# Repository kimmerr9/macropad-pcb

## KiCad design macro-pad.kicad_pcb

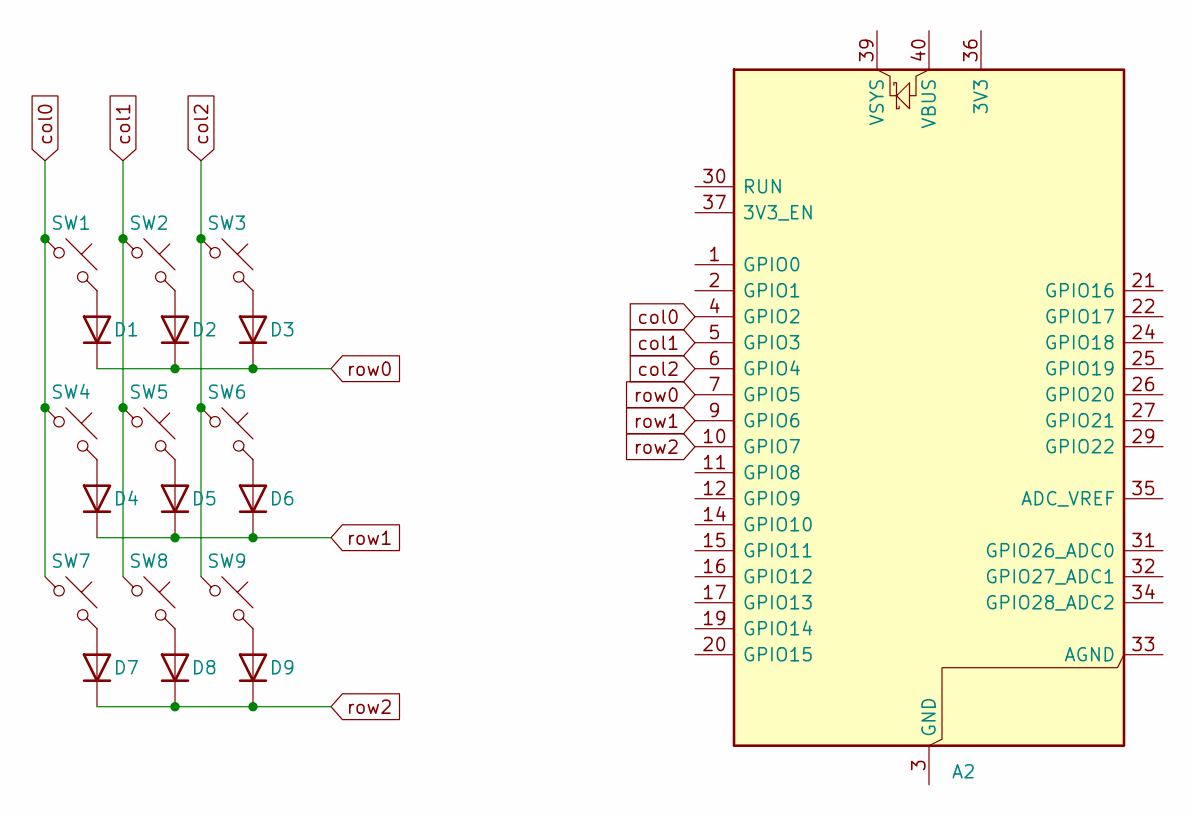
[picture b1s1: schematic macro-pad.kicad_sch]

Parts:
A2: RaspberryPi_Pico_W; RaspberryPi_Pico_W_SMD_HandSolder
D1, D2, D3, D4, D5, D6, D7, D8, D9: 1N4148; D_DO-35_SOD27_P7.62mm_Horizontal
SW1, SW2, SW3, SW4, SW5, SW6, SW7, SW8, SW9: SW_Push_45deg; SW_Cherry_MX_1.00u_PCB

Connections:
unnamed: A2.3 (GND), A2.8 (GND), A2.13 (GND), A2.18 (GND), A2.23 (GND), A2.28 (GND), A2.38 (GND)
unnamed: D1.2 (A), SW1.2
unnamed: D2.2 (A), SW2.2
unnamed: D3.2 (A), SW3.2
unnamed: D4.2 (A), SW4.2
unnamed: D5.2 (A), SW5.2
unnamed: D6.2 (A), SW6.2
unnamed: D7.2 (A), SW7.2
unnamed: D8.2 (A), SW8.2
unnamed: D9.2 (A), SW9.2
col0: A2.4 (GPIO2), SW1.1, SW4.1, SW7.1
col1: A2.5 (GPIO3), SW2.1, SW5.1, SW8.1
col2: A2.6 (GPIO4), SW3.1, SW6.1, SW9.1
row0: A2.7 (GPIO5), D1.1 (K), D2.1 (K), D3.1 (K)
row1: A2.9 (GPIO6), D4.1 (K), D5.1 (K), D6.1 (K)
row2: A2.10 (GPIO7), D7.1 (K), D8.1 (K), D9.1 (K)

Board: 2 copper layers, 19 parts (0 on the bottom side), 16 nets, no tracks yet.

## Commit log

2025-08-09 init commit
2025-08-09 keyboard matrix and microcontroller sch
2025-08-10 finished sch, inprogress pcb
